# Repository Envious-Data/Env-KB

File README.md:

# Env-KB
 A custom mechanical keyboard inspired by the CFTKB Mysterium.
 
- Project Name: EnvKB80
- Nickname: Delirium

### About:
This is a raspberry pi pico powered keyboard I designed as I wanted something similar to a CFTKB Mysterium but easier to solder and a bit more robustly designed.

### Firmware
Pre-compiled firmwares can be found [here](https://github.com/Envious-Data/EnvKB-QMK/tree/main/_PREBUILTFIRMWARES)
- to flash a raspberry pi pico or any RP2040 board you need to hold the bootsel button while plugging in the USB, it'll show up as a USB drive called RP2-boot, you can then drag and drop a UF2 firmware file onto the pico, it will reboot its self.

### Parts
- 1x Type-C-31-M-14
- 90x 1n4148 DO-35
- 90x MX keyboard switches (5 pin advised if without switch plate)
- 3x 5.1K 1/4W resistors
- 1x 3mm LED
- 1x 1x04 2.54mm pin socket (optional oled)
- 1x Panasonic EVQPU SMD switch (optional reset)
- raspberry pi pico

- 10x m2 female standoffs 10mm 
- 20x m2 screws <5mm

(this list may not be totally accurate since I often forget what has changed inbetween when the readme is updated.

### Building
Most part orientations should be marked on the PCB however it is important to note that you NEED to connect the pads under the MCU to the respective pads on the board for USB to work, you also need 5.1K resistors to work with USB PD compatible ports.

the type-c port may be difficult for some to solder so use loads of flux and minimal amounts of solder, its best to solder the large 4 outer pins of the shell first.

### Why a RPI Pico?
uh well why not, I think it would be a nice example for people to use as a example.
When I came up with the idea of this keyboard there was 1 other raspberry pi pico keyboard so I decided it would be cool to make a keyboard.

### PCBWAY

[PCBWAY](http://pcbway.com) Kindly sponsored a batch of PCBs of which you can see [pictures](_pictures/Hotswap/) of inside the pictures folder.

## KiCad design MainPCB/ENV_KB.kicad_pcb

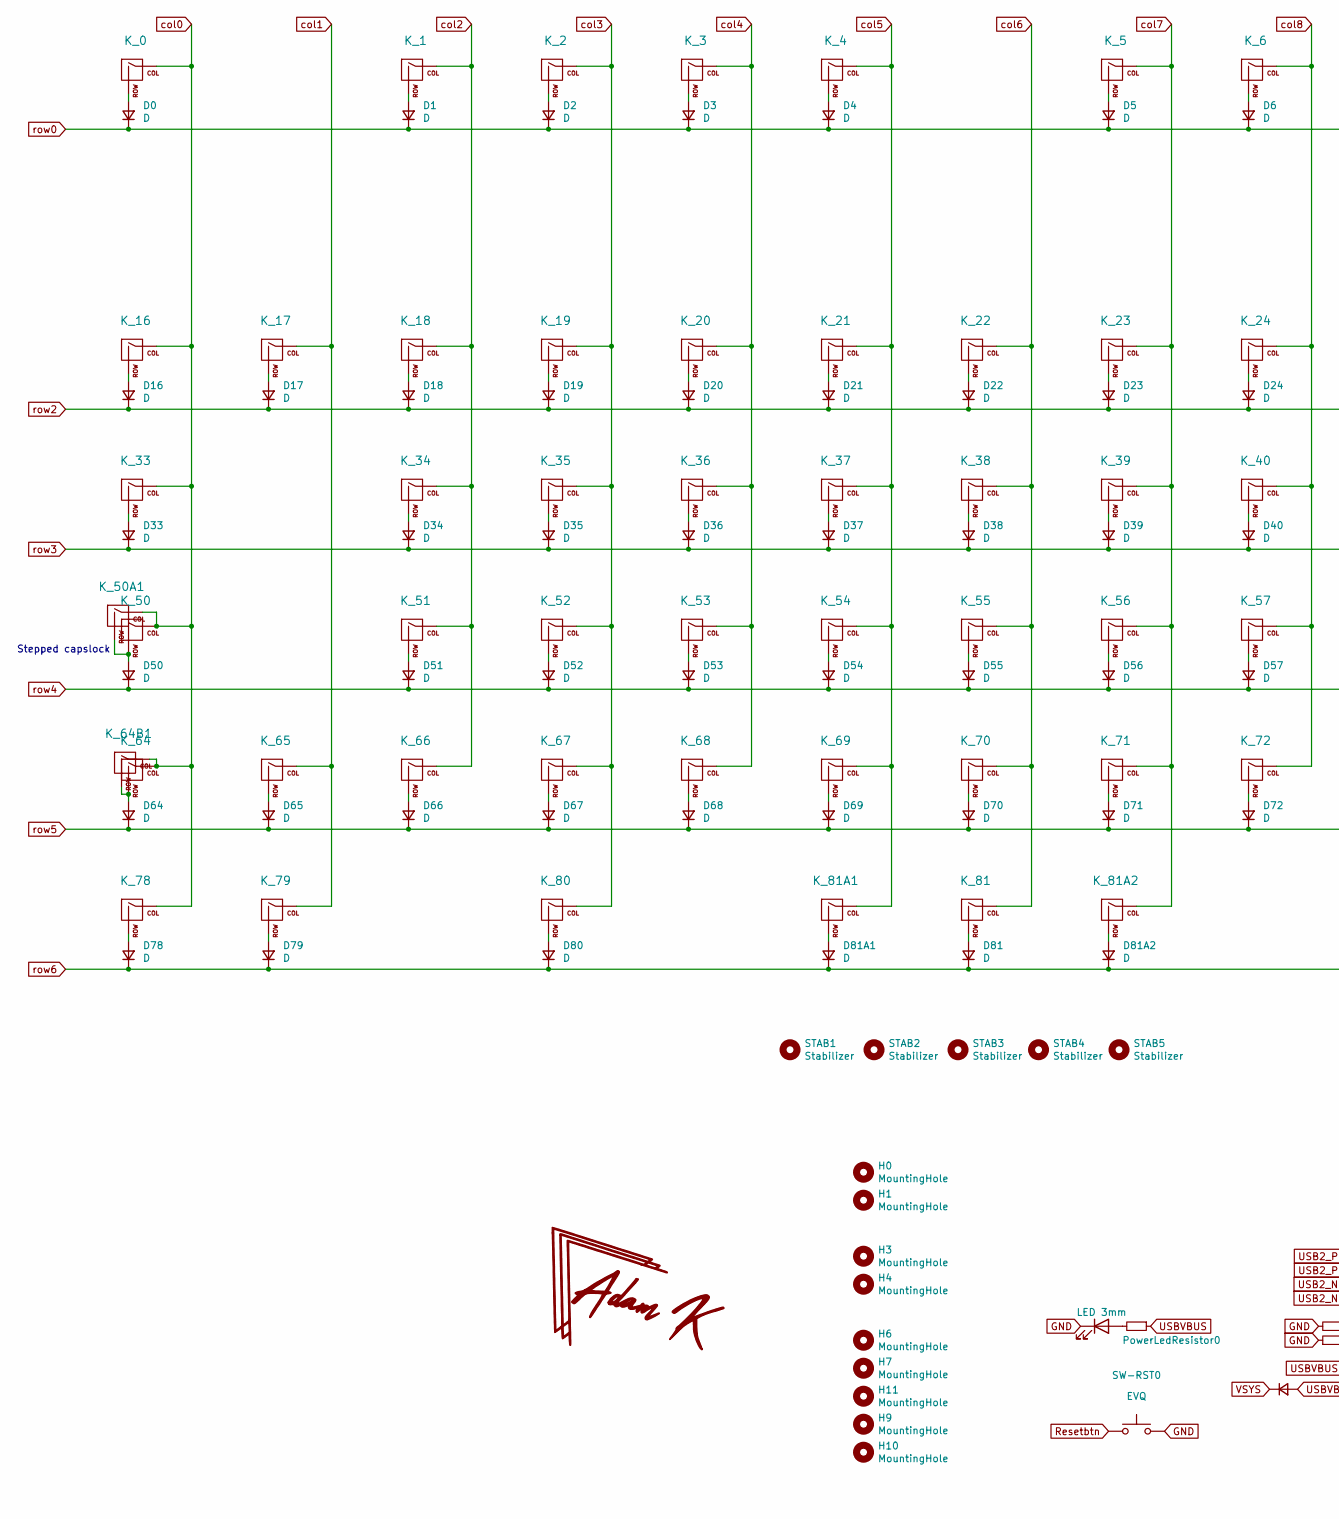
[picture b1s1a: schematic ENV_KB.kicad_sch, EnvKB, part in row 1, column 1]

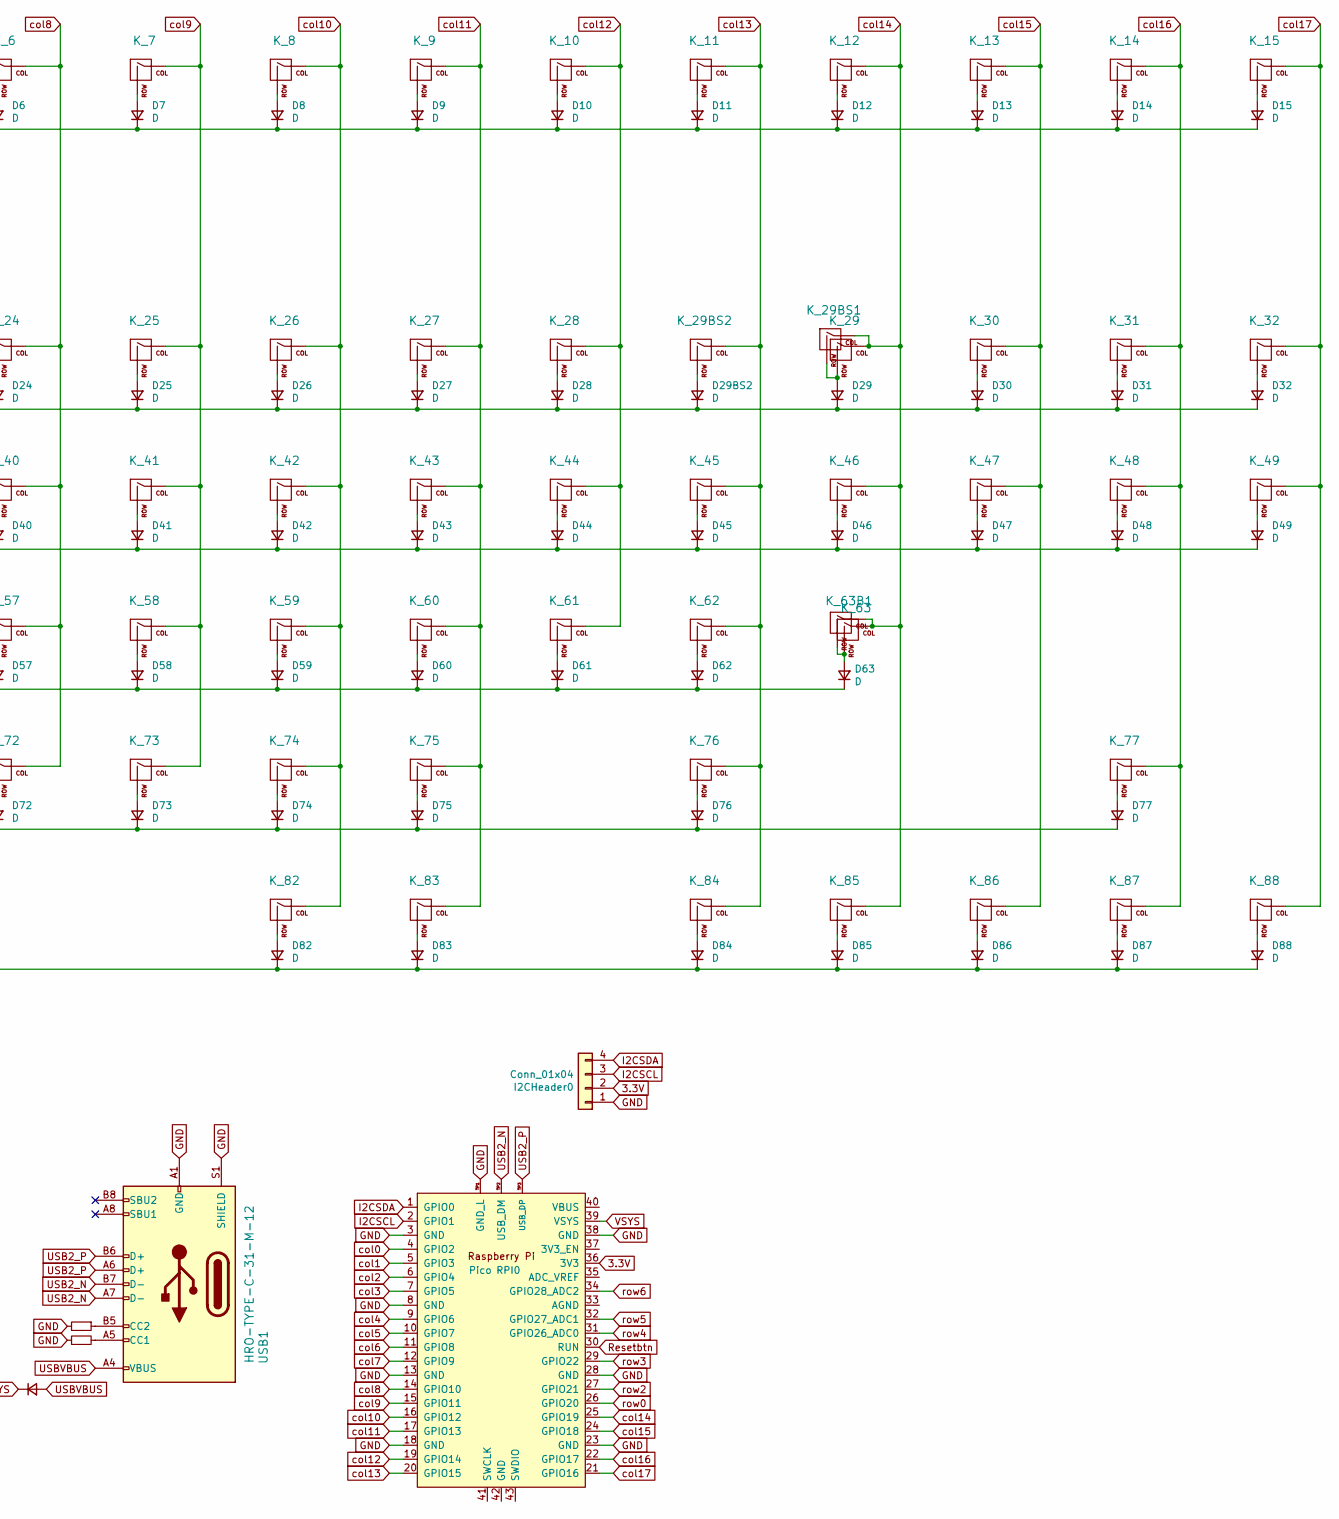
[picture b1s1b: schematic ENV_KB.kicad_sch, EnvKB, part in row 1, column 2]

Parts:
D0, D1, D2, D3, D4, D5, D6, D7, D8, D9, D10, D11, D12, D13, D14, D15, D16, D17, D18, D19, D20, D21, D22, D23, D24, D25, D26, D27, D28, D29, D29BS2, D30, D31, D32, D33, D34, D35, D36, D37, D38, D39, D40, D41, D42, D43, D44, D45, D46, D47, D48, D49, D50, D51, D52, D53, D54, D55, D56, D57, D58, D59, D60, D61, D62, D63, D64, D65, D66, D67, D68, D69, D70, D71, D72, D73, D74, D75, D76, D77, D78, D79, D80, D81, D81A1, D81A2, D82, D83, D84, D85, D86, D87, D88: D; D_DO-35_SOD27_P7.62mm_Horizontal
D89: 1n4002; D_DO-35_SOD27_P7.62mm_Horizontal
H0, H1, H3, H4, H6, H7, H9, H10, H11: MountingHole; MountingHole_2.2mm_M2_Pad
I2CHeader0: Conn_01x04; PinSocket_1x04_P2.54mm_Vertical
K_0, K_1, K_2, K_3, K_4, K_5, K_6, K_7, K_8, K_9, K_10, K_11, K_12, K_13, K_14, K_15, K_16, K_17, K_18, K_19, K_20, K_21, K_22, K_23, K_24, K_25, K_26, K_27, K_28, K_29, K_29BS1, K_29BS2, K_30, K_31, K_32, K_34, K_35, K_36, K_37, K_38, K_39, K_40, K_41, K_42, K_43, K_44, K_45, K_47, K_48, K_49, K_51, K_52, K_53, K_54, K_55, K_56, K_57, K_58, K_59, K_60, K_61, K_62, K_65, K_66, K_67, K_68, K_69, K_70, K_71, K_72, K_73, K_74, K_75, K_77, K_81, K_81A1, K_81A2, K_86, K_87, K_88: KEYSW; MXOnly-1U-NoLED
K_33, K_46: KEYSW; MXOnly-1.5U-NoLED
K_50: KEYSW; MXOnly-1.75U-NoLED
K_50A1, K_64, K_78, K_79, K_80, K_82, K_83, K_84, K_85: KEYSW; MXOnly-1.25U-NoLED
K_63: MX-NoLED; MXOnly-ISO-ROTATED-ReversedStabilizers-NoLED
K_63B1: MX-NoLED; MXOnly-2.25U-NoLED
K_64B1: KEYSW; MXOnly-2.25U-NoLED
K_76: KEYSW; MXOnly-2.75U-NoLED
PowerLED0: LED 3mm; LED_D3.0mm
PowerLedResistor0: 47K Resistor; R_Axial_DIN0207_L6.3mm_D2.5mm_P7.62mm_Horizontal; LCSC C17513
RESISTOR0, RESISTOR1: 5.1k; R_Axial_DIN0207_L6.3mm_D2.5mm_P7.62mm_Horizontal; LCSC C25905
RPI0: Pico; RPi_Pico_SMD_TH
STAB1, STAB2, STAB3, STAB4, STAB5: Stabilizer; Stabilizer_Cherry_MX_2u
SW-RST0: EVQ; Panasonic_EVQPUL_EVQPUC
USB1: HRO-TYPE-C-31-M-12; USB_C_TYPE-C-31-M-14; LCSC C165948

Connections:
3.3V: I2CHeader0.2, RPI0.36 (3V3)
GND: I2CHeader0.1, PowerLED0.1 (K), RESISTOR0.2, RESISTOR1.1, RPI0.3 (GND), RPI0.8 (GND), RPI0.13 (GND), RPI0.18 (GND), RPI0.23 (GND), RPI0.28 (GND), RPI0.38 (GND), RPI0.TP1 (GND_L), SW-RST0.2, USB1.A1 (GND), USB1.A12 (GND), USB1.B1 (GND), USB1.B12 (GND), USB1.S1 (SHIELD)
I2CSCL: I2CHeader0.3, RPI0.2 (GPIO1)
I2CSDA: I2CHeader0.4, RPI0.1 (GPIO0)
unnamed 4: D0.2 (A), K_0.2 (ROW); also elsewhere on the board
unnamed: D1.2 (A), K_1.2 (ROW)
unnamed: D2.2 (A), K_2.2 (ROW)
unnamed: D3.2 (A), K_3.2 (ROW)
unnamed: D4.2 (A), K_4.2 (ROW)
unnamed: D5.2 (A), K_5.2 (ROW)
unnamed: D6.2 (A), K_6.2 (ROW)
unnamed: D7.2 (A), K_7.2 (ROW)
unnamed: D8.2 (A), K_8.2 (ROW)
unnamed: D9.2 (A), K_9.2 (ROW)
unnamed: D10.2 (A), K_10.2 (ROW)
unnamed: D11.2 (A), K_11.2 (ROW)
unnamed: D12.2 (A), K_12.2 (ROW)
unnamed: D13.2 (A), K_13.2 (ROW)
unnamed: D14.2 (A), K_14.2 (ROW)
unnamed: D15.2 (A), K_15.2 (ROW)
unnamed: D16.2 (A), K_16.2 (ROW)
unnamed: D17.2 (A), K_17.2 (ROW)
unnamed: D18.2 (A), K_18.2 (ROW)
unnamed: D19.2 (A), K_19.2 (ROW)
unnamed: D20.2 (A), K_20.2 (ROW)
unnamed: D21.2 (A), K_21.2 (ROW)
unnamed: D22.2 (A), K_22.2 (ROW)
unnamed: D23.2 (A), K_23.2 (ROW)
unnamed: D24.2 (A), K_24.2 (ROW)
unnamed: D25.2 (A), K_25.2 (ROW)
unnamed: D26.2 (A), K_26.2 (ROW)
unnamed: D27.2 (A), K_27.2 (ROW)
unnamed: D28.2 (A), K_28.2 (ROW)
unnamed: D29.2 (A), K_29.2 (ROW), K_29BS1.2 (ROW)
unnamed: D29BS2.2 (A), K_29BS2.2 (ROW)
unnamed: D30.2 (A), K_30.2 (ROW)
unnamed: D31.2 (A), K_31.2 (ROW)
unnamed: D32.2 (A), K_32.2 (ROW)
unnamed: D33.2 (A), K_33.2 (ROW)
unnamed: D34.2 (A), K_34.2 (ROW)
unnamed: D35.2 (A), K_35.2 (ROW)
unnamed: D36.2 (A), K_36.2 (ROW)
unnamed: D37.2 (A), K_37.2 (ROW)
unnamed: D38.2 (A), K_38.2 (ROW)
unnamed: D39.2 (A), K_39.2 (ROW)
unnamed: D40.2 (A), K_40.2 (ROW)
unnamed: D41.2 (A), K_41.2 (ROW)
unnamed: D42.2 (A), K_42.2 (ROW)
unnamed: D43.2 (A), K_43.2 (ROW)
unnamed: D44.2 (A), K_44.2 (ROW)
unnamed: D45.2 (A), K_45.2 (ROW)
unnamed: D46.2 (A), K_46.2 (ROW)
unnamed: D47.2 (A), K_47.2 (ROW)
unnamed: D48.2 (A), K_48.2 (ROW)
unnamed: D49.2 (A), K_49.2 (ROW)
unnamed: D50.2 (A), K_50.2 (ROW), K_50A1.2 (ROW)
unnamed: D51.2 (A), K_51.2 (ROW)
unnamed: D52.2 (A), K_52.2 (ROW)
unnamed: D53.2 (A), K_53.2 (ROW)
unnamed: D54.2 (A), K_54.2 (ROW)
unnamed: D55.2 (A), K_55.2 (ROW)
unnamed: D56.2 (A), K_56.2 (ROW)
unnamed: D57.2 (A), K_57.2 (ROW)
unnamed: D58.2 (A), K_58.2 (ROW)
unnamed: D59.2 (A), K_59.2 (ROW)
unnamed: D60.2 (A), K_60.2 (ROW)
unnamed: D61.2 (A), K_61.2 (ROW)
unnamed: D62.2 (A), K_62.2 (ROW)
unnamed: D63.2 (A), K_63.2 (ROW), K_63B1.2 (ROW)
unnamed: D64.2 (A), K_64.2 (ROW), K_64B1.2 (ROW)
unnamed: D65.2 (A), K_65.2 (ROW)
unnamed: D66.2 (A), K_66.2 (ROW)
unnamed: D67.2 (A), K_67.2 (ROW)
unnamed: D68.2 (A), K_68.2 (ROW)
unnamed: D69.2 (A), K_69.2 (ROW)
unnamed: D70.2 (A), K_70.2 (ROW)
unnamed: D71.2 (A), K_71.2 (ROW)
unnamed: D72.2 (A), K_72.2 (ROW)
unnamed: D73.2 (A), K_73.2 (ROW)
unnamed: D74.2 (A), K_74.2 (ROW)
unnamed: D75.2 (A), K_75.2 (ROW)
unnamed: D76.2 (A), K_76.2 (ROW)
unnamed: D77.2 (A), K_77.2 (ROW)
unnamed: D78.2 (A), K_78.2 (ROW)
unnamed: D79.2 (A), K_79.2 (ROW)
unnamed: D80.2 (A), K_80.2 (ROW)
unnamed: D81.2 (A), K_81.2 (ROW)
unnamed: D81A1.2 (A), K_81A1.2 (ROW)
unnamed: D81A2.2 (A), K_81A2.2 (ROW)
unnamed: D82.2 (A), K_82.2 (ROW)
unnamed: D83.2 (A), K_83.2 (ROW)
unnamed: D84.2 (A), K_84.2 (ROW)
unnamed: D85.2 (A), K_85.2 (ROW)
unnamed: D86.2 (A), K_86.2 (ROW)
unnamed: D87.2 (A), K_87.2 (ROW)
unnamed: D88.2 (A), K_88.2 (ROW)
unnamed: PowerLED0.2 (A), PowerLedResistor0.2
unnamed: RESISTOR0.1, USB1.B5 (CC2)
unnamed: RESISTOR1.2, USB1.A5 (CC1)
Resetbtn: RPI0.30 (RUN), SW-RST0.1
USB2_N: RPI0.TP2 (USB_DM), USB1.A7 (D-), USB1.B7 (D-)
USB2_P: RPI0.TP3 (USB_DP), USB1.A6 (D+), USB1.B6 (D+)
USBVBUS: D89.2 (A), PowerLedResistor0.1, USB1.A4 (VBUS), USB1.A9 (VBUS), USB1.B4 (VBUS), USB1.B9 (VBUS)
VSYS: D89.1 (K), RPI0.39 (VSYS)
col0: K_0.1 (COL), K_16.1 (COL), K_33.1 (COL), K_50.1 (COL), K_50A1.1 (COL), K_64.1 (COL), K_64B1.1 (COL), K_78.1 (COL), RPI0.4 (GPIO2); also elsewhere on the board
col1: K_17.1 (COL), K_65.1 (COL), K_79.1 (COL), RPI0.5 (GPIO3)
col2: K_1.1 (COL), K_18.1 (COL), K_34.1 (COL), K_51.1 (COL), K_66.1 (COL), RPI0.6 (GPIO4)
col3: K_2.1 (COL), K_19.1 (COL), K_35.1 (COL), K_52.1 (COL), K_67.1 (COL), K_80.1 (COL), RPI0.7 (GPIO5)
col4: K_3.1 (COL), K_20.1 (COL), K_36.1 (COL), K_53.1 (COL), K_68.1 (COL), RPI0.9 (GPIO6)
col5: K_4.1 (COL), K_21.1 (COL), K_37.1 (COL), K_54.1 (COL), K_69.1 (COL), K_81A1.1 (COL), RPI0.10 (GPIO7)
col6: K_22.1 (COL), K_38.1 (COL), K_55.1 (COL), K_70.1 (COL), K_81.1 (COL), RPI0.11 (GPIO8)
col7: K_5.1 (COL), K_23.1 (COL), K_39.1 (COL), K_56.1 (COL), K_71.1 (COL), K_81A2.1 (COL), RPI0.12 (GPIO9)
col8: K_6.1 (COL), K_24.1 (COL), K_40.1 (COL), K_57.1 (COL), K_72.1 (COL), RPI0.14 (GPIO10)
col9: K_7.1 (COL), K_25.1 (COL), K_41.1 (COL), K_58.1 (COL), K_73.1 (COL), RPI0.15 (GPIO11)
col10: K_8.1 (COL), K_26.1 (COL), K_42.1 (COL), K_59.1 (COL), K_74.1 (COL), K_82.1 (COL), RPI0.16 (GPIO12)
col11: K_9.1 (COL), K_27.1 (COL), K_43.1 (COL), K_60.1 (COL), K_75.1 (COL), K_83.1 (COL), RPI0.17 (GPIO13)
col12: K_10.1 (COL), K_28.1 (COL), K_44.1 (COL), K_61.1 (COL), RPI0.19 (GPIO14)
col13: K_11.1 (COL), K_29BS2.1 (COL), K_45.1 (COL), K_62.1 (COL), K_76.1 (COL), K_84.1 (COL), RPI0.20 (GPIO15)
col14: K_12.1 (COL), K_29.1 (COL), K_29BS1.1 (COL), K_46.1 (COL), K_63.1 (COL), K_63B1.1 (COL), K_85.1 (COL), RPI0.25 (GPIO19)
col15: K_13.1 (COL), K_30.1 (COL), K_47.1 (COL), K_86.1 (COL), RPI0.24 (GPIO18)
col16: K_14.1 (COL), K_31.1 (COL), K_48.1 (COL), K_77.1 (COL), K_87.1 (COL), RPI0.22 (GPIO17)
col17: K_15.1 (COL), K_32.1 (COL), K_49.1 (COL), K_88.1 (COL), RPI0.21 (GPIO16)
row0: D0.1 (K), D1.1 (K), D2.1 (K), D3.1 (K), D4.1 (K), D5.1 (K), D6.1 (K), D7.1 (K), D8.1 (K), D9.1 (K), D10.1 (K), D11.1 (K), D12.1 (K), D13.1 (K), D14.1 (K), D15.1 (K), RPI0.26 (GPIO20)
row2: D16.1 (K), D17.1 (K), D18.1 (K), D19.1 (K), D20.1 (K), D21.1 (K), D22.1 (K), D23.1 (K), D24.1 (K), D25.1 (K), D26.1 (K), D27.1 (K), D28.1 (K), D29.1 (K), D29BS2.1 (K), D30.1 (K), D31.1 (K), D32.1 (K), RPI0.27 (GPIO21)
row3: D33.1 (K), D34.1 (K), D35.1 (K), D36.1 (K), D37.1 (K), D38.1 (K), D39.1 (K), D40.1 (K), D41.1 (K), D42.1 (K), D43.1 (K), D44.1 (K), D45.1 (K), D46.1 (K), D47.1 (K), D48.1 (K), D49.1 (K), RPI0.29 (GPIO22)
row4: D50.1 (K), D51.1 (K), D52.1 (K), D53.1 (K), D54.1 (K), D55.1 (K), D56.1 (K), D57.1 (K), D58.1 (K), D59.1 (K), D60.1 (K), D61.1 (K), D62.1 (K), D63.1 (K), RPI0.31 (GPIO26_ADC0)
row5: D64.1 (K), D65.1 (K), D66.1 (K), D67.1 (K), D68.1 (K), D69.1 (K), D70.1 (K), D71.1 (K), D72.1 (K), D73.1 (K), D74.1 (K), D75.1 (K), D76.1 (K), D77.1 (K), RPI0.32 (GPIO27_ADC1)
row6: D78.1 (K), D79.1 (K), D80.1 (K), D81.1 (K), D81A1.1 (K), D81A2.1 (K), D82.1 (K), D83.1 (K), D84.1 (K), D85.1 (K), D86.1 (K), D87.1 (K), D88.1 (K), RPI0.34 (GPIO28_ADC2)

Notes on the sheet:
Stepped capslock

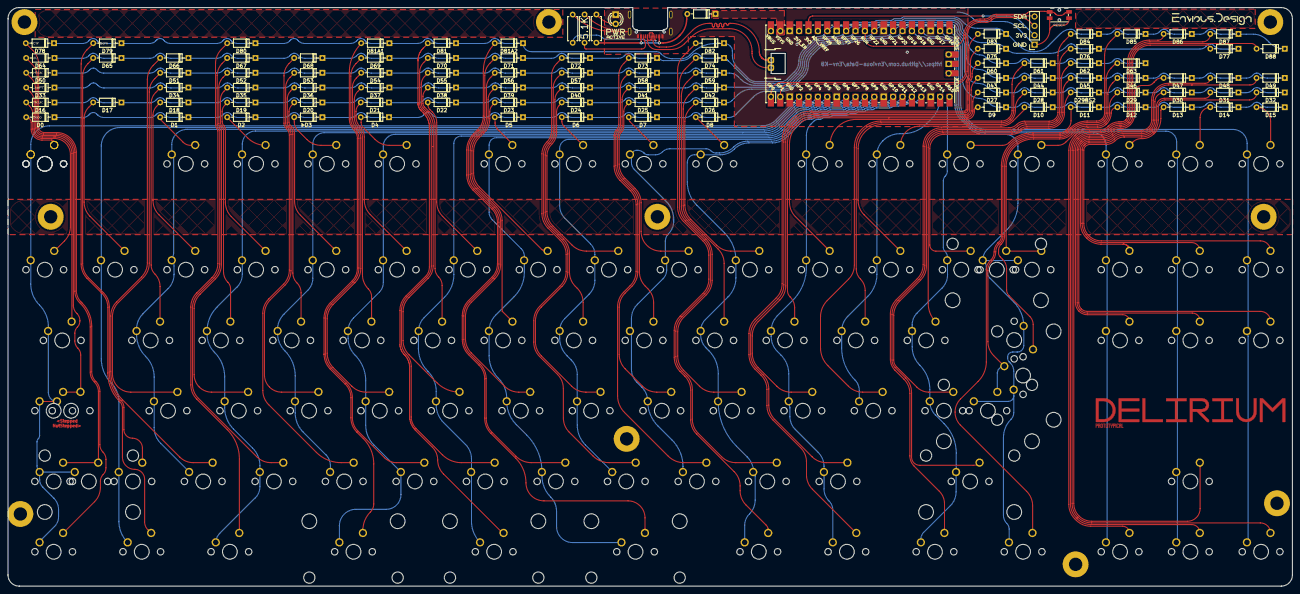
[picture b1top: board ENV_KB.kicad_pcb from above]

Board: 2 copper layers, 347.0 x 156.3 mm, 232 parts (0 on the bottom side), 128 nets.

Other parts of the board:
H4#2: MountingHole; MountingHole_2.2mm_M2_Pad
K_0#2: KEYSW; MXOnly-1U-NoLED
kibuzzard-628ADF99, kibuzzard-628ADF99#2: G***; kibuzzard-628ADF99
kibuzzard-628AE7EF: G***; kibuzzard-628AE7EF
kibuzzard-628AE7FB: G***; kibuzzard-628AE7FB
kibuzzard-628AE8A6: G***; kibuzzard-628AE8A6
kibuzzard-628AE061, kibuzzard-628AE061#2: G***; kibuzzard-628AE061
kibuzzard-628AE80F: G***; kibuzzard-628AE80F
kibuzzard-628AE82F: G***; kibuzzard-628AE82F
kibuzzard-628AE768: G***; kibuzzard-628AE768
kibuzzard-628AE805: G***; kibuzzard-628AE805
kibuzzard-628AE860: G***; kibuzzard-628AE860
kibuzzard-628AE868: G***; kibuzzard-628AE868
kibuzzard-628AE874: G***; kibuzzard-628AE874
kibuzzard-628AE882: G***; kibuzzard-628AE882
kibuzzard-628AE933: G***; kibuzzard-628AE933
kibuzzard-628AE966: G***; kibuzzard-628AE966
kibuzzard-628AEA91: G***; kibuzzard-628AEA91
kibuzzard-6250C4E7: G***; kibuzzard-6250C4E7

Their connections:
unnamed 4: K_0#2.2 (ROW); also elsewhere on the board
col0: K_0#2.1 (COL); also elsewhere on the board

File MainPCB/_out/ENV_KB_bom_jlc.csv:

"Comment","Designator","Footprint","LCSC Part #"
"D","D7,D8,D9,D10,D11,D12,D13,D14,D15,D16,D17,D18,D19,D20,D21,D22,D23,D24,D25,D26,D27,D28,D29,D30,D31,D32,D33,D34,D35,D36,D37,D38,D39,D40,D41,D42,D43,D44,D45,D47,D48,D49,D50,D51,D52,D53,D54,D55,D56,D57,D58,D59,D60,D61,D62,D64,D65,D66,D67,D68,D69,D70,D71,D72,D73,D74,D75,D76,D77,D78,D79,D6,D5,D4,D3,D2,D1,D0,D88,D87,D86,D85,D84,D83,D82,D81,D80,D46,D63","D_DO-35_SOD27_P7.62mm_Horizontal","no_part_number"
"MountingHole","H9,H10,H7,H6,H4,H1,H3,H0","MountingHole_2.2mm_M2_Pad","no_part_number"
"Conn_01x04","I2CHeader0","PinSocket_1x04_P2.54mm_Vertical","no_part_number"
"KEYSW","K_0,K_1,K_2,K_3,K_4,K_5,K_6,K_7,K_8,K_9,K_10,K_11,K_12,K_13,K_14,K_15,K_16,K_17,K_18,K_19,K_20,K_21,K_22,K_23,K_24,K_25,K_26,K_27,K_28,K_30,K_31,K_32,K_34,K_35,K_36,K_37,K_38,K_39,K_40,K_41,K_42,K_43,K_44,K_45,K_47,K_48,K_49,K_51,K_52,K_53,K_54,K_55,K_56,K_57,K_58,K_59,K_60,K_61,K_62,K_65,K_66,K_67,K_68,K_69,K_70,K_71,K_72,K_73,K_74,K_75,K_77,K_86,K_87,K_88","MXOnly-1U-NoLED","no_part_number"
"KEYSW","K_29","MXOnly-2U-NoLED","no_part_number"
"KEYSW","K_33,K_46","MXOnly-1.5U-NoLED","no_part_number"
"KEYSW","K_50","MXOnly-1.75U-NoLED","no_part_number"
"MX-NoLED","K_63","MXOnly-ISO-ROTATED-ReversedStabilizers-NoLED","no_part_number"
"MX-NoLED","K_63B1","MXOnly-2.25U-NoLED","no_part_number"
"KEYSW","K_64,K_78,K_79,K_80,K_82,K_83,K_84,K_85","MXOnly-1.25U-NoLED","no_part_number"
"KEYSW","K_64B1","MXOnly-2.25U-NoLED","no_part_number"
"KEYSW","K_76","MXOnly-2.75U-NoLED","no_part_number"
"KEYSW","K_81","MXOnly-6.25U-ReversedStabilizers-NoLED","no_part_number"
"LED 0402","PowerLED0","LED_0402_1005Metric","no_part_number"
"47K Resistor 0402","PowerLedResistor0","R_0402_1005Metric","C17513"
"5.1kohm 0402","RESISTOR1,RESISTOR0","R_0402_1005Metric","C25905"
"Pico","RPI0","RPi_Pico_SMD_TH","no_part_number"
"Stabilizer","STAB1","Stabilizer_Cherry_MX_2u","no_part_number"
"EVQ","SW-RST0","Panasonic_EVQPUL_EVQPUC","no_part_number"
"HRO-TYPE-C-31-M-12","USB1","USB_C_TYPE-C-31-M-14","C165948"

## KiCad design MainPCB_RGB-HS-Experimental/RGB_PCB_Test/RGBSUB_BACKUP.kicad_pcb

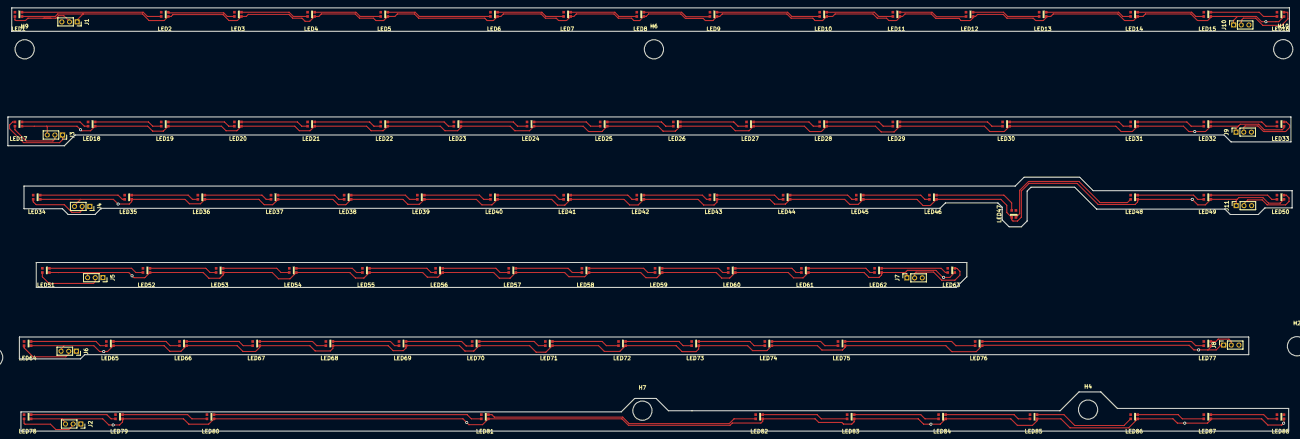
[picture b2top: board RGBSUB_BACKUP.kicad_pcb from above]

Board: 2 copper layers, 334.4 x 110.2 mm, 108 parts (0 on the bottom side), 94 nets.

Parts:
H0, H1, H2, H3, H4, H6, H7, H9, H10: MountingHole; MountingHole_5mm
J1, J2, J3, J4, J5, J6, J7, J8, J9, J10, J11: Conn_01x04; PinSocket_1x03_P2.00mm_Vertical
LED1, LED2, LED3, LED4, LED5, LED6, LED7, LED8, LED9, LED10, LED11, LED12, LED13, LED14, LED15, LED16, LED17, LED18, LED19, LED20, LED21, LED22, LED23, LED24, LED25, LED26, LED27, LED28, LED29, LED30, LED31, LED32, LED33, LED34, LED35, LED36, LED37, LED38, LED39, LED40, LED41, LED42, LED43, LED44, LED45, LED46, LED47, LED48, LED49, LED50, LED51, LED52, LED53, LED54, LED55, LED56, LED57, LED58, LED59, LED60, LED61, LED62, LED63, LED64, LED65, LED66, LED67, LED68, LED69, LED70, LED71, LED72, LED73, LED74, LED75, LED76, LED77, LED78, LED79, LED80, LED81, LED82, LED83, LED84, LED85, LED86, LED87, LED88: SK6812MINI-E; WS2812-2020

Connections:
GND: H0.1, H1.1, H2.1, H3.1, H4.1, H6.1, H7.1, H9.1, H10.1, J1.3, J2.1, J3.1, J4.1, J5.1, J6.1, J7.3, J8.3, J9.3, J10.3, J11.3, LED1.3, LED2.3, LED3.3, LED4.3, LED5.3, LED6.3, LED7.3, LED8.3, LED9.3, LED10.3, LED11.3, LED12.3, LED13.3, LED14.3, LED15.3, LED16.3, LED17.3, LED18.3, LED19.3, LED20.3, LED21.3, LED22.3, LED23.3, LED24.3, LED25.3, LED26.3, LED27.3, LED28.3, LED29.3, LED30.3, LED31.3, LED32.3, LED33.3, LED34.3, LED35.3, LED36.3, LED37.3, LED38.3, LED39.3, LED40.3, LED41.3, LED42.3, LED43.3, LED44.3, LED45.3, LED46.3, LED47.3, LED48.3, LED49.3, LED50.3, LED51.3, LED52.3, LED53.3, LED54.3, LED55.3, LED56.3, LED57.3, LED58.3, LED59.3, LED60.3, LED61.3, LED62.3, LED63.3, LED64.3, LED65.3, LED66.3, LED67.3, LED68.3, LED69.3, LED70.3, LED71.3, LED72.3, LED73.3, LED74.3, LED75.3, LED76.3, LED77.3, LED78.3, LED79.3, LED80.3, LED81.3, LED82.3, LED83.3, LED84.3, LED85.3, LED86.3, LED87.3, LED88.3
LEDPIN: J1.2, LED1.4
unnamed: J2.2, LED78.4
unnamed: J3.2, LED17.4
unnamed: J4.2, LED34.4
unnamed: J5.2, LED51.4
unnamed: J6.2, LED64.4
unnamed: J7.2, LED63.2
unnamed: J8.2, LED77.2
unnamed: J9.2, LED33.2
unnamed: J10.2, LED16.2
unnamed: J11.2, LED50.2
unnamed: LED1.2, LED2.4
unnamed: LED2.2, LED3.4
unnamed: LED3.2, LED4.4
unnamed: LED4.2, LED5.4
unnamed: LED5.2, LED6.4
unnamed: LED6.2, LED7.4
unnamed: LED7.2, LED8.4
unnamed: LED8.2, LED9.4
unnamed: LED10.2, LED11.4
unnamed: LED9.2, LED10.4
unnamed: LED11.2, LED12.4
unnamed: LED12.2, LED13.4
unnamed: LED13.2, LED14.4
unnamed: LED14.2, LED15.4
unnamed: LED15.2, LED16.4
unnamed: LED17.2, LED18.4
unnamed: LED18.2, LED19.4
unnamed: LED19.2, LED20.4
unnamed: LED20.2, LED21.4
unnamed: LED21.2, LED22.4
unnamed: LED22.2, LED23.4
unnamed: LED23.2, LED24.4
unnamed: LED24.2, LED25.4
unnamed: LED25.2, LED26.4
unnamed: LED26.2, LED27.4
unnamed: LED27.2, LED28.4
unnamed: LED28.2, LED29.4
unnamed: LED29.2, LED30.4
unnamed: LED30.2, LED31.4
unnamed: LED31.2, LED32.4
unnamed: LED32.2, LED33.4
unnamed: LED34.2, LED35.4
unnamed: LED35.2, LED36.4
unnamed: LED36.2, LED37.4
unnamed: LED37.2, LED38.4
unnamed: LED38.2, LED39.4
unnamed: LED39.2, LED40.4
unnamed: LED40.2, LED41.4
unnamed: LED41.2, LED42.4
unnamed: LED42.2, LED43.4
unnamed: LED43.2, LED44.4
unnamed: LED44.2, LED45.4
unnamed: LED45.2, LED46.4
unnamed: LED46.2, LED47.4
unnamed: LED47.2, LED48.4
unnamed: LED48.2, LED49.4
unnamed: LED49.2, LED50.4
unnamed: LED51.2, LED52.4
unnamed: LED52.2, LED53.4
unnamed: LED53.2, LED54.4
unnamed: LED54.2, LED55.4
unnamed: LED55.2, LED56.4
unnamed: LED56.2, LED57.4
unnamed: LED57.2, LED58.4
unnamed: LED58.2, LED59.4
unnamed: LED59.2, LED60.4
unnamed: LED60.2, LED61.4
unnamed: LED61.2, LED62.4
unnamed: LED62.2, LED63.4
unnamed: LED64.2, LED65.4
unnamed: LED65.2, LED66.4
unnamed: LED66.2, LED67.4
unnamed: LED67.2, LED68.4
unnamed: LED68.2, LED69.4
unnamed: LED69.2, LED70.4
unnamed: LED70.2, LED71.4
unnamed: LED71.2, LED72.4
unnamed: LED72.2, LED73.4
unnamed: LED73.2, LED74.4
unnamed: LED74.2, LED75.4
unnamed: LED75.2, LED76.4
unnamed: LED76.2, LED77.4
unnamed: LED78.2, LED79.4
unnamed: LED79.2, LED80.4
unnamed: LED80.2, LED81.4
unnamed: LED81.2, LED82.4
unnamed: LED82.2, LED83.4
unnamed: LED83.2, LED84.4
unnamed: LED84.2, LED85.4
unnamed: LED85.2, LED86.4
unnamed: LED87.2, LED88.4
USBVBUS: J1.1, J2.3, J3.3, J4.3, J5.3, J6.3, J7.1, J8.1, J9.1, J10.1, J11.1, LED1.1, LED2.1, LED3.1, LED4.1, LED5.1, LED6.1, LED7.1, LED8.1, LED9.1, LED10.1, LED11.1, LED12.1, LED13.1, LED14.1, LED15.1, LED16.1, LED17.1, LED18.1, LED19.1, LED20.1, LED21.1, LED22.1, LED23.1, LED24.1, LED25.1, LED26.1, LED27.1, LED28.1, LED29.1, LED30.1, LED31.1, LED32.1, LED33.1, LED34.1, LED35.1, LED36.1, LED37.1, LED38.1, LED39.1, LED40.1, LED41.1, LED42.1, LED43.1, LED44.1, LED45.1, LED46.1, LED47.1, LED48.1, LED49.1, LED50.1, LED51.1, LED52.1, LED53.1, LED54.1, LED55.1, LED56.1, LED57.1, LED58.1, LED59.1, LED60.1, LED61.1, LED62.1, LED63.1, LED64.1, LED65.1, LED66.1, LED67.1, LED68.1, LED69.1, LED70.1, LED71.1, LED72.1, LED73.1, LED74.1, LED75.1, LED76.1, LED77.1, LED78.1, LED79.1, LED80.1, LED81.1, LED82.1, LED83.1, LED84.1, LED85.1, LED86.1, LED87.1, LED88.1

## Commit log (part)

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2021-02-16 Add KiCad Bits
    all the KiCad bits for this project.
2021-02-16 Renamed Files to correct names
2021-02-16 Updated Ratsnest
2021-02-17 Updated Schematic
2021-02-17 More Progress
2021-02-18 Adjusted Diodes, Traces + added logo
2021-02-18 Undid diode mess / Done rest of Switch Traces
2021-02-18 Replaced Diodes in horizontal stack
2021-02-19 possible solution to MCU orientation and space usage dilemma
2021-02-19 Finished remaining traces, need to do TP# Vbus and GND for usb now.
2021-02-20 general housekeeping.
2021-02-21 some additional final updates before having a first batch made
2021-02-21 This should be Ready.
2021-02-21 replaced Micro B with Type C due to parts avaliability
2021-02-21 some random changes
2021-02-25 Made universal ground pane
2021-02-25 some adjustments
2021-02-27 more adjustments
    this version i have sent to JLCPCB
2021-03-04 Change of lib-tabel's to use relative paths
2021-03-04 Adjustments for Rev.B
    added a place for the I2C header and traces + a USB power LED and a few small tweaks
2021-03-05 Added image/updated README
2021-03-05 Upgrade to #d4e7e293a4b4e92c8b19c42b1b3e7286d16a446a
    Adjustments for Rev.B
    added a place for the I2C header and traces + a USB power LED and a few small tweaks
2021-03-05 Remove not needen log file and added .gitignore file
2021-03-05 Corrections, Part Numbers, Cleanups, etc
    I removed a couple of un-needed libraries finally and corrected a bunch of stuff.
    also added LSCS part numbers in the schematic
    probably some other stuff I forgot
2021-03-07 various things, silk screen bits, cleaning up, etc
2021-03-08 resized PCB a bit (156.5x348.5)
2021-03-17 Placing of the Keys and Track to the IO Expander Header for Spare Pin on IO Expander
2021-03-17 added keymap py for KMK
2021-03-18 Addtion of Solder Briges for Addresing of the Expander might re add an smaler one later Addtion of Pullups for I2C lines Removeal of Pinheader for IO Expander Fix Fuckup on Col 20 is used two times F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
2021-03-18 Change: chaning schematic to use rows of main keyboard to save boot time TODO: Rerunning of the tracks to comply with schematic
2021-03-18 Reouting Tracks Rerunning tacks to use Rows of main keyboard Update TO DO
2021-03-18 just got rid of some un-wanted graphics
2021-03-19 Fixed errors with keymap
2021-03-20 Added some M2 mount holes
2021-03-21 added monting holes on the keypad and rerun traces that were interfering
2021-03-21 addtion of breakout Connector for unsused port of IO Expander Fix Trace from K 104 being to close to drilling holes
2021-03-21 addtion of Leds for Num, Cabs and Scroll Lock update Todo
2021-03-21 Relocated state LEDs to above the arrow keys and moved an few traces
2021-03-22 Fix trouh holes of K 96
2021-03-24 Small change to allow normal usage
2021-03-26 Added Build guide and parts list PDF
2021-03-26 did a woops on the PDF link lol.
2021-03-28 Upload of keyboard-layout.json the file for the key layouter plugin
2021-03-29 Initial Ansi Support
    adding support to fit ansi backslash and enter key
    probably needs some double checking +this would be incompatible with the current keymap unless you dont mind a non functional enter key and a ANSI backslash which does enter instead.
2021-03-29 ANSI updates and cleaning up
    just neatened up some traces, added some markings.
2021-03-29 ANSI support in keymap
    In theory this should be correct lol because I moved enter down a row and I ANSI backslash where ISO enter was and piggybacked ANSI enter off the new position of ISO ENTER if that makes any sense at 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
2021-04-03 Uploaded KMK files for keyboard
    This is a optimized version of KMK with the LED fix and the legacy keymap for this keyboard.
    if your pico runs circuitpython you can drag and drop the contents of this zip onto your pico.
2021-04-06 Designing a basic plate design that can be exported to SVG
    Attempting to use KICAD for mechanical CAD design, Im utilizing the user layers to work on a plate design
2021-04-06 more plate design work + screwholes
    I would like for this keyboard to feel like a solid unit like a individual object not an assembly of a few, something sturdy and light.
2021-04-07 Housekeeping
    this folder is getting very messy so I its high time for a bit of spring cleaning.
2021-04-07 Front plate design adjustments to fit MCU
2021-04-09 Adding more mount holes and some alignment adjustments
2021-04-09 moved a bunch of traces and made the board slimmer
2021-04-09 Added layer example and changed LED To be lit via PWM so its not as bright
2021-04-09 compiled new circuitpython UF2 and updated firmware readme
2021-04-09 link woopises.
2021-04-11 General housekeeping
2021-04-12 Reset MCU on Exception being raised
    This is a workaround for when the host computer resets and causes a error in Circuitpython or KMK (not sure which) but to stop the keyboard from becoming useless without reconnecting it this will now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
2021-04-15 Removed un-needed via and adjusted traces for ground plane fill.
2021-04-15 Updated keymap for non legacy keyboard
2021-04-16 Some small updates and corrections
2021-04-17 added B§F-100o back to Symbole Lib Back pasting of my changes move of drill hole lower right side
2021-04-17 General changes and fixes
2021-04-17 Corrected Gerber to match JLCPCB's Guide
2021-04-18 Slight rebrand to comply with some stuff.
2021-04-20 Updated Gerber Zip and Added Pictures of PCB
2021-04-20 Added an extra photo
2021-04-20 Corrected an error with the laser cut SVG
2021-05-05 some plate adjustments and smaller reset button
2021-05-07 Changed mount hole size and adjusted placement
2021-05-10 Redesigned Plate, resized board, adjusted mount holes
2021-05-12 Updated Gerber bits and laser cut dxfs
2021-05-12 a few small adjustments to traces and pads
2021-05-14 Added a quick and dirty build guide
2021-05-14 Fixed typo
2021-05-20 Cleaned up Repo and made blank bottom PCB
2021-05-20 Changed Button to B3U from EVQ + smaller LED resistor
2021-05-22 Re aligned all diodes and re-did traces for all diodes
2021-05-22 added Gerber for optional switch plate
2021-05-22 changed type-c port and re-did some bits
2021-05-24 some small alignment tweaks and corrections
2021-05-27 Added bat file for useful JLCPCB compatible CPL and BOM generation
2021-05-27 Decided to rename KB from Providentia to Delirium because it sounds like Mysterium and is also ironic
2021-05-27 Updated Gerbers and generated BOM/CPL
2021-05-31 General checkover, Generated upto date Gerbers for JLCPCB
2021-06-11 increased Resistor value for led as it was too bright.
2021-06-14 Implemented Hotswap sockets onto RGB version
2021-06-14 Small Corrections to traces
2021-06-15 Updated Guide and documentation / Generated Gerbers for RGB keyboard
2021-06-15 cleanup and some small fixes as per DRC
2021-06-17 Corrected a mistake in the silkscreen, overlapping a contributor initials and footprint
2021-06-23 Updated the keymap for the Rev#0 board to include some examples and stuff
2021-06-26 Started work on embedded Rp2040 version
2021-06-28 added a example for using a oled on the keyboard, needs the libraries mentioned in the code
2021-06-29 Added a guide for ordering my PCBs via JLCPCB
2021-07-06 added experimental QMK firmware files for keyboard
2021-07-14 Changed all mount holes to M2 and added some pads around the holes to avoid scratches being visible on pcbs
2021-07-19 Mostly Completed this design but needs overall improvement
2021-07-23 enlarged the switch cutouts to fit over the switches instead.
2021-07-28 replaced buck boost with a LDO (AP2127K-3.3)
2021-08-02 Swapped Reset button for cheaper Alps SKRK
2021-08-16 corrected all DRC Errors, all vias on pads as well as separated vbus and vsys in the schematic properly.
2021-08-31 started work on a test gasket/spacer type thing for front and back.
2021-09-03 adjusted gasket plates some more.
2021-09-04 made a folder for gfx stuff and added a couple base files.
2021-09-06 Generated JLCPCB Compatible Gerber, BOM and CPL for HS/RGB Version
2021-09-07 shrunk the PCBs width down to 347mm to comply with JLCPCBs max size for 4 layers.
2021-09-07 General tweaks and cleanup, misc bits.
2021-09-08 (ignore last commit to these files) I removed all the "K" markers for orientation as its part of the footprints silkscreen as is.
2021-09-14 updated PCB to have through hole parts except type-c port.
2021-09-14 Generated Gerber zip for (mostly) through hole version
2021-09-14 committing this file to make sure I dont do a dumb
    its the switch plate for the Rev#1 PCB that has 3.2mm drill holes, I switched it to M2 later. aka the current files on this repo.
2021-09-29 re-done (all) key matrix traces
2021-10-01 corrected a couple of small issues
2021-10-05 generated laser cut files for current PCB version, changed footprint size of resistors to 1/4 instead of 1/8w
2021-10-05 couple small tweaks, cleared Eco1 for later use.
2021-10-06 Fixed silkscreen and various other issues
    some traces were too close for comfort so Ive gone and spaced some stuff out and moved some other traces away from the edge of the pcb through a pair of vias
2021-10-12 some tweaks and corrections, fixed some issues on rp2040 version
2021-10-12 some updated DXFs, using them to learn fusion360
2021-10-20 Changed silkscreen and logo on main version and also adjusted some spacing and traces a bit more
2021-10-22 corrected some random duplicated traces and leftover tails.
2021-10-25 fixed components that were no longer connected and added cutouts for directly soldering MCU onto PCB
2021-10-25 minor markers and tweaks
2021-10-25 small tweaks to some traces and spacing
2021-10-26 Corrected resistor footprint and adjusted placement, added cutout for direct mount usb castellation.
2021-10-26 added LED cutout on user layer
2021-10-26 Generated updated gerbers.
2021-11-02 added temporary DXF for later personal use.
2021-11-15 fixed a trace running too close to some switch holes
2021-11-15 Corrected CPL
2021-11-25 added cutout for USB TP pad soldering and a JST connector in the schematic
2021-11-26 removed lib
2021-11-26 added library as submodule
2021-11-26 generated updated gerber
2021-12-01 updated QMK builds
2021-12-01 updated instructions and firmware bits
2021-12-05 added submodule back
2021-12-05 sorted library stuff for RGB version
2021-12-10 Started Rework of RP2040 version (again)
2021-12-17 various tweaks, adjustments and corrections with new usb port
2022-02-04 Added decoupling capacitors per LED
2022-02-18 generated updated gerbers for checking price
2022-03-14 added dual footprints and removed experimental version
2022-03-29 Added ANSI layout keys back.
2022-04-01 some various adjustments
2022-04-08 overall fixup and update of main Version
2022-04-11 added a link to prebuilt QMK firmwares and updated main PCB version with curvy tracks.
2022-04-15 moved some stuff about and updated readme
2022-04-15 updated some outdated info.
2022-04-15 Corrected a Mistake in the placement of ANSI Backslash
2022-04-15 some various fixes, tweaks and adjustments
2022-04-17 some various fixes and tweaks
2022-04-21 added mount holes to user layer
2022-04-21 fixed? ansi+iso+hotswap support I think but also file cleanup
2022-05-03 various tweaks and adjustments, Generated Gerber however there is an issue with overlapping footprints in part selection
2022-05-20 Tidied up some stuff and updated the logo.
2022-05-23 swapped footprint of various parts, updated the logo and tweaked some traces
2022-05-26 Overhauled original board deisgn and modified RGB board design, made sure native fillets were used, 45 or 90
2022-05-30 various trace tweaks to make the board look more consistent
2022-06-02 roundified hotswap board and general corrections to other boards, RP2040 DRC fixes mainly
2022-06-05 Added Stepped left shift for orig version
2022-06-07 fixed some traces I didnt like
2022-06-10 tiny tweaks
2022-06-11 Updated WRL model
2022-06-11 Parity changes between RGB and non RGB HS versions
2022-06-16 Unified board shape/size and mount holes + re-centered USB port to new size
2022-06-16 slight correction to usb port position
2022-07-25 removed RP2040 version as it no longer fits with the direction of this project.
2022-07-30 Swapped VBUS power to VSYS and fixed edge cut issues.
2022-11-16 fixed all DRC errors on HS version
2023-01-19 huge repo cleanup
2023-01-19 created backplate with exportable outline
2023-01-19 lots more work towards making this available
2023-01-19 Generated Gerbers
2023-01-26 moved Kicad files into their own folder
2023-04-15 fixed some issues with clearances, traces and zones.
2023-09-24 commit forgotten changes and update readme
2024-04-09 added KLE Raw data for firmware generation
